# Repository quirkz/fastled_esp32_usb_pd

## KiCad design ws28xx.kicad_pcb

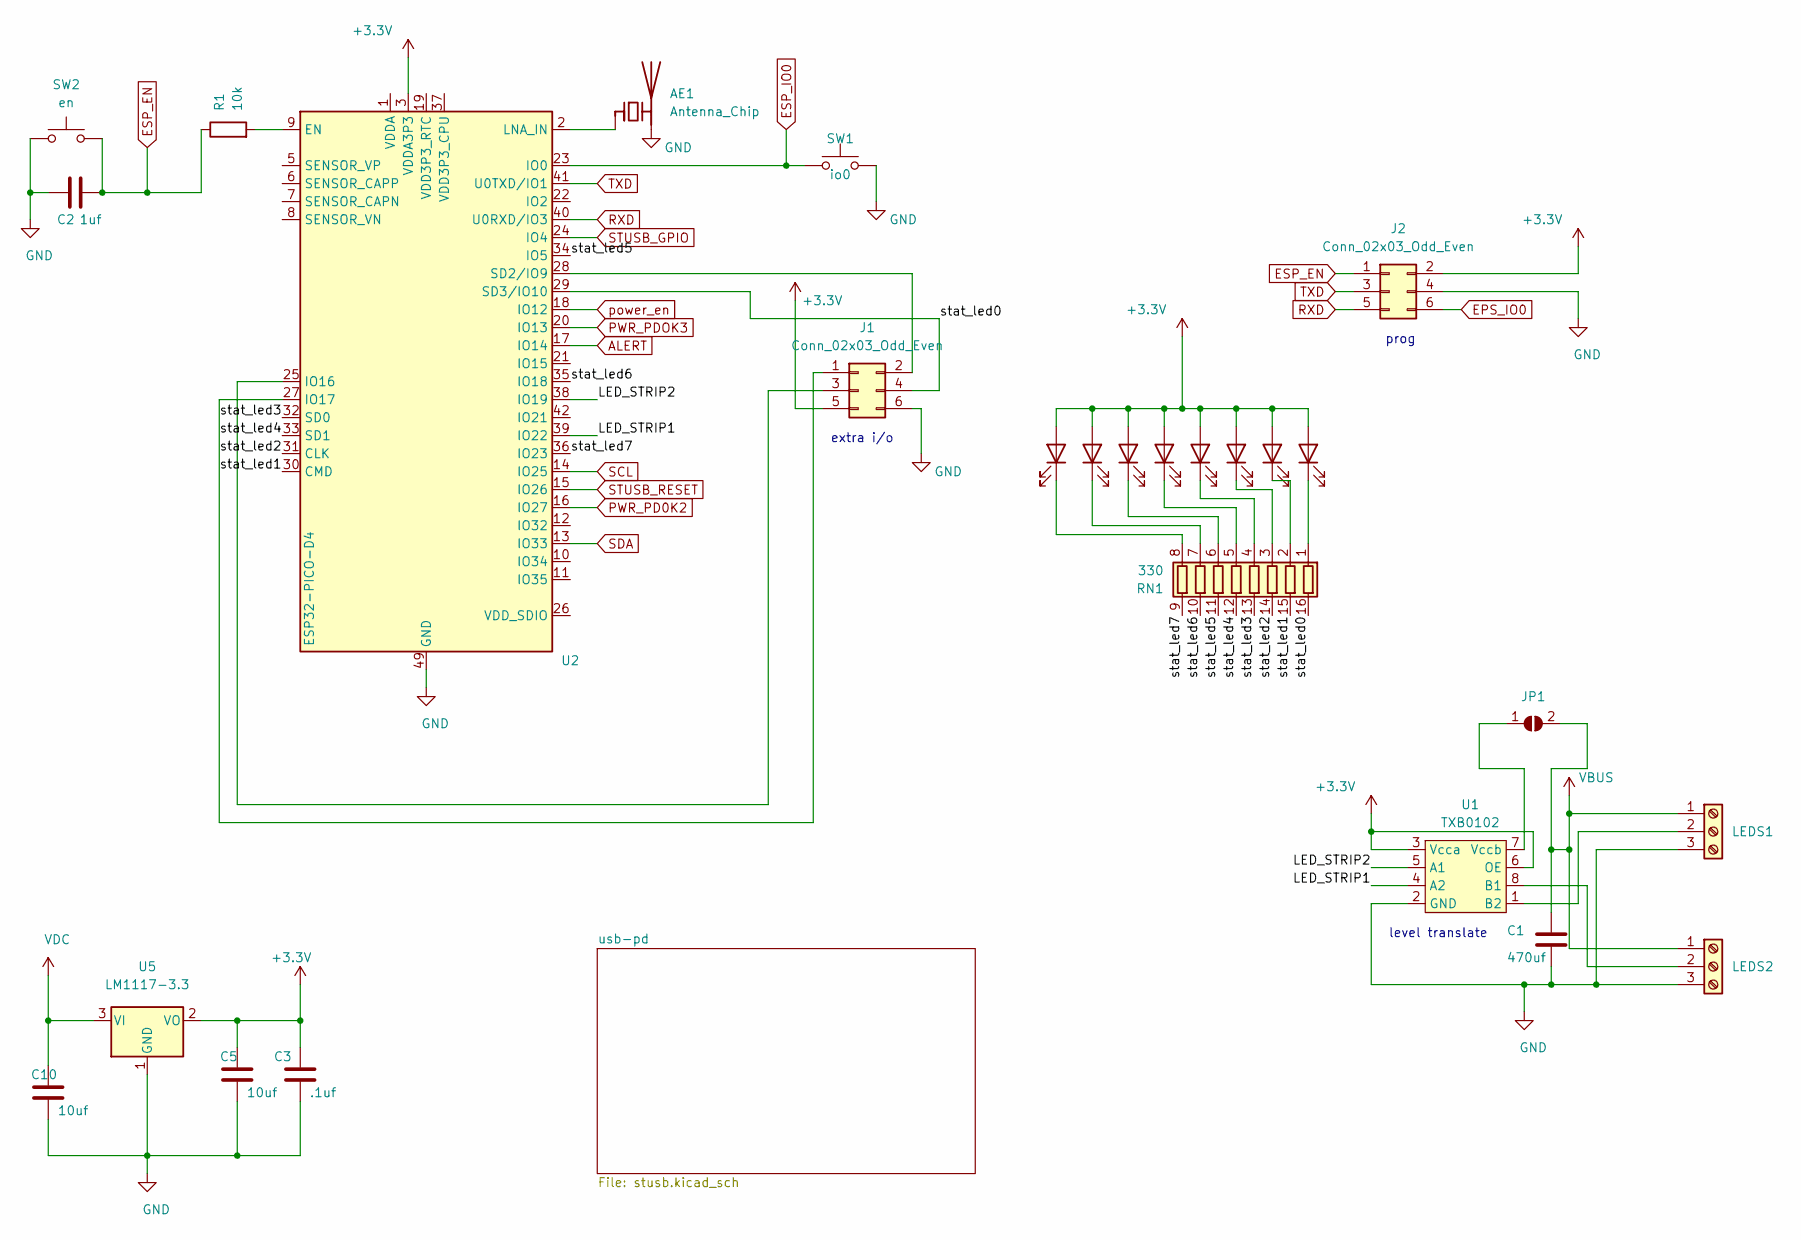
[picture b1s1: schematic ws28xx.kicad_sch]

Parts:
AE1: Antenna_Chip; Texas_SWRA117D_2.4GHz_Right
C1: 470uf; C_Elec_10x10.2
C2: 1uf; C_0603_1608Metric
C3: .1uf; C_0603_1608Metric
C5, C10: 10uf; C_0805_2012Metric
D1, D2, D3, D4, D5, D6, D7, D8: LED; LED_0603_1608Metric
J1, J2: Conn_02x03_Odd_Even; PinHeader_2x03_P1.27mm_Vertical
JP1: SolderJumper_2_Open; PinHeader_1x02_P1.27mm_Vertical
LEDS1: Screw_Terminal_01x0; TerminalBlock_Phoenix_PT-1,5-3-3.5-H_1x03_P3.50mm_Horizontal
LEDS2: Screw_Terminal_01x03; TerminalBlock_Phoenix_PT-1,5-3-3.5-H_1x03_P3.50mm_Horizontal
R1: 10k; R_0603_1608Metric
RN1: 330; R_Array_Convex_8x0602
SW1: io0; SW_Push_1P1T_NO_Vertical
SW2: en; SW_Push_1P1T_NO_Vertical
U1: TXB0102; SOIC-8
U2: ESP32-PICO-D4; QFN-48-1EP_7x7mm_P0.5mm_EP5.3x5.3mm
U5: LM1117-3.3; SOT-223

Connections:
+3V3: C3.1, C5.1, D1.2 (A), D2.2 (A), D3.2 (A), D4.2 (A), D5.2 (A), D6.2 (A), D7.2 (A), D8.2 (A), J1.5, J2.2, U1.3 (Vcca), U1.6 (OE), U2.3 (VDDA3P3), U2.4 (VDDA3P3), U5.2 (VO); also elsewhere on the board
/LED_STRIP1: U1.4 (A2), U2.39 (IO22)
/LED_STRIP2: U1.5 (A1), U2.38 (IO19)
/stat_led0: J1.4, RN1.16 (R1.2), U2.29 (SD3/IO10)
/stat_led1: RN1.15 (R2.2), U2.30 (CMD)
/stat_led2: RN1.14 (R3.2), U2.31 (CLK)
/stat_led3: RN1.13 (R4.2), U2.32 (SD0)
/stat_led4: RN1.12 (R5.2), U2.33 (SD1)
/stat_led5: RN1.11 (R6.2), U2.34 (IO5)
/stat_led6: RN1.10 (R7.2), U2.35 (IO18)
/stat_led7: RN1.9 (R8.2), U2.36 (IO23)
ALERT: U2.17 (IO14); also elsewhere on the board
EPS_IO0: J2.6
ESP_EN: C2.2, J2.1, R1.1, SW2.2; also elsewhere on the board
ESP_IO0: SW1.1, U2.23 (IO0); also elsewhere on the board
GND: AE1.2 (PCB_Trace), C1.2, C2.1, C3.2, C5.2, C10.2, J1.6, J2.4, LEDS1.3, LEDS2.3, SW1.2, SW2.1, U1.2 (GND), U2.49 (GND), U5.1 (GND); also elsewhere on the board
unnamed: AE1.1 (FEED), U2.2 (LNA_IN)
unnamed: D1.1 (K), RN1.8 (R8.1)
unnamed: D2.1 (K), RN1.7 (R7.1)
unnamed: D3.1 (K), RN1.5 (R5.1)
unnamed: D4.1 (K), RN1.6 (R6.1)
unnamed: D5.1 (K), RN1.4 (R4.1)
unnamed: D6.1 (K), RN1.2 (R2.1)
unnamed: D7.1 (K), RN1.1 (R1.1)
unnamed: D8.1 (K), RN1.3 (R3.1)
unnamed: J1.1, U2.27 (IO17)
unnamed: J1.2, U2.28 (SD2/IO9)
unnamed: J1.3, U2.25 (IO16)
unnamed: JP1.1 (A), U1.7 (Vccb)
unnamed: LEDS1.2, U1.1 (B2)
unnamed: LEDS2.2, U1.8 (B1)
unnamed: R1.2, U2.9 (EN)
unnamed: U2.1 (VDDA), U2.43 (VDDA), U2.46 (VDDA)
PWR_PD0K2: U2.16 (IO27); also elsewhere on the board
PWR_PDOK3: U2.20 (IO13); also elsewhere on the board
RXD: J2.5, U2.40 (U0RXD/IO3); also elsewhere on the board
SCL: U2.14 (IO25); also elsewhere on the board
SDA: U2.13 (IO33); also elsewhere on the board
STUSB_GPIO: U2.24 (IO4); also elsewhere on the board
STUSB_RESET: U2.15 (IO26); also elsewhere on the board
TXD: J2.3, U2.41 (U0TXD/IO1); also elsewhere on the board
VBUS: C1.1, JP1.2 (B), LEDS1.1, LEDS2.1; also elsewhere on the board
VDC: C10.1, U5.3 (VI); also elsewhere on the board
power_en: U2.18 (IO12); also elsewhere on the board

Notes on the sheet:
extra i/o
prog
level translate

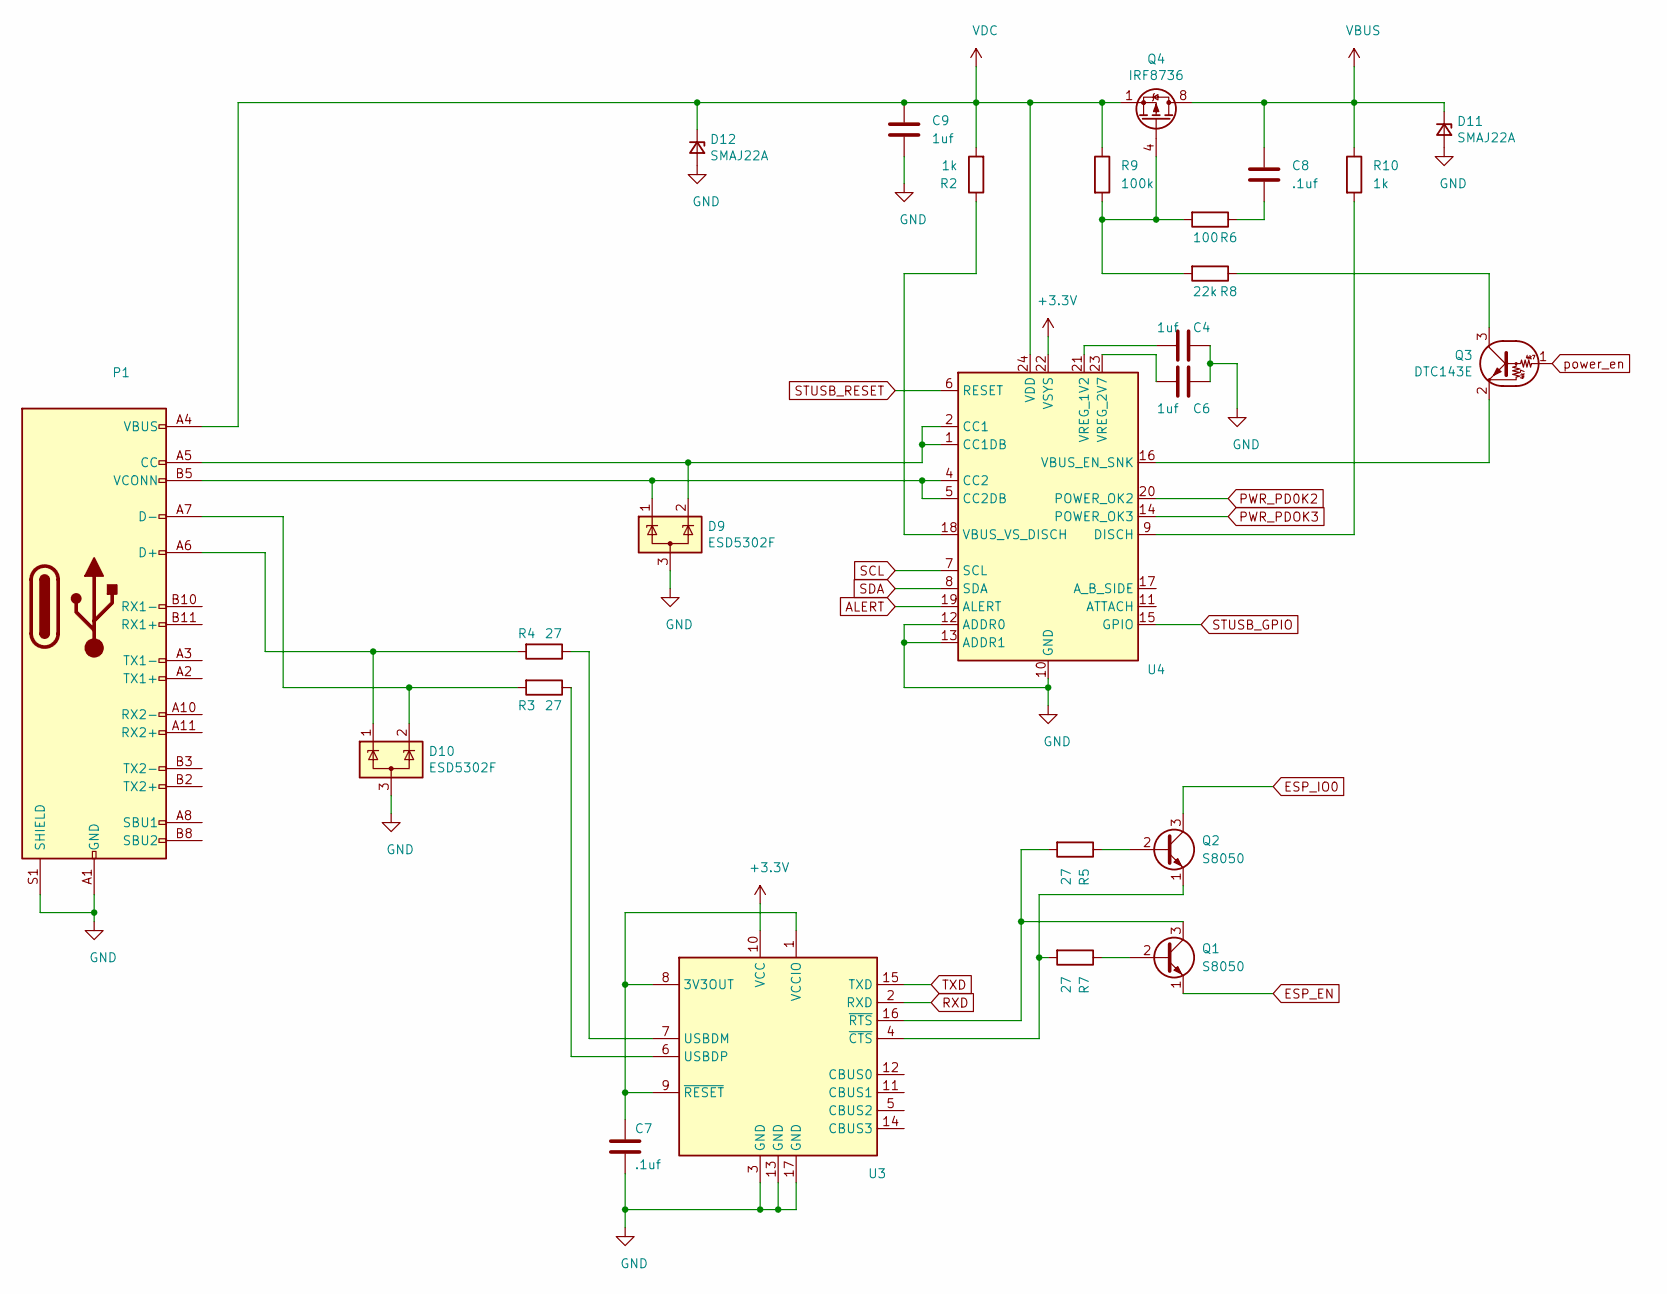
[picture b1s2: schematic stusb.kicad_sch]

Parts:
C4, C6, C9: 1uf; C_0603_1608Metric
C7, C8: .1uf; C_0603_1608Metric
D9, D10: ESD5302F; SOT-23
D11, D12: SMAJ22A; D_SMA
P1: USB_C_Plug; USB_C_Receptacle_Palconn_UTC16-G
Q1, Q2: S8050; SOT-23
Q3: DTC143E; SOT-323_SC-70
Q4: IRF8736; SOIC-8_3.9x4.9mm_P1.27mm
R2, R10: 1k; R_0603_1608Metric
R3, R4, R5, R7: 27; R_0603_1608Metric
R6: 100; R_0603_1608Metric
R8: 22k; R_0603_1608Metric
R9: 100k; R_0603_1608Metric
U3: FT230XQ; QFN-16-1EP_4x4mm_P0.65mm_EP2.1x2.1mm
U4: STUSB4500QTR; QFN-24-1EP_4x4mm_P0.5mm_EP2.7x2.7mm

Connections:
+3V3: U3.10 (VCC), U4.22 (VSYS); also elsewhere on the board
ALERT: U4.19 (ALERT); also elsewhere on the board
ESP_EN: Q1.1 (E); also elsewhere on the board
ESP_IO0: Q2.3 (C); also elsewhere on the board
GND: C4.1, C6.1, C7.2, C9.2, D9.3 (A), D10.3 (A), D11.2 (A), D12.2 (A), P1.A1 (GND), P1.A12 (GND), P1.B1 (GND), P1.B12 (GND), P1.S1 (SHIELD), U3.3 (GND), U3.13 (GND), U3.17 (GND), U4.10 (GND), U4.12 (ADDR0), U4.13 (ADDR1), U4.25 (GND); also elsewhere on the board
unnamed: C4.2, U4.21 (VREG_1V2)
unnamed: C6.2, U4.23 (VREG_2V7)
unnamed: C7.1, U3.1 (VCCIO), U3.8 (3V3OUT), U3.9 (~RESET)
unnamed: C8.2, R6.1
unnamed: D9.1 (K), P1.B5 (VCONN), U4.4 (CC2), U4.5 (CC2DB)
unnamed: D9.2 (K), P1.A5 (CC), U4.1 (CC1DB), U4.2 (CC1)
unnamed: D10.1 (K), P1.A6 (D+), R4.2
unnamed: D10.2 (K), P1.A7 (D-), R3.2
unnamed: Q1.2 (B), R7.1
unnamed: Q1.3 (C), R5.2, U3.16 (~RTS)
unnamed: Q2.1 (E), R7.2, U3.4 (~CTS)
unnamed: Q2.2 (B), R5.1
unnamed: Q3.2 (E), U4.16 (VBUS_EN_SNK)
unnamed: Q3.3 (C), R8.1
unnamed: Q4.4 (G), R6.2, R8.2, R9.2
unnamed: R2.1, U4.18 (VBUS_VS_DISCH)
unnamed: R3.1, U3.6 (USBDP)
unnamed: R4.1, U3.7 (USBDM)
unnamed: R10.2, U4.9 (DISCH)
PWR_PD0K2: U4.20 (POWER_OK2); also elsewhere on the board
PWR_PDOK3: U4.14 (POWER_OK3); also elsewhere on the board
RXD: U3.2 (RXD); also elsewhere on the board
SCL: U4.7 (SCL); also elsewhere on the board
SDA: U4.8 (SDA); also elsewhere on the board
STUSB_GPIO: U4.15 (GPIO); also elsewhere on the board
STUSB_RESET: U4.6 (RESET); also elsewhere on the board
TXD: U3.15 (TXD); also elsewhere on the board
VBUS: C8.1, D11.1 (K), Q4.5 (D), Q4.6 (D), Q4.7 (D), Q4.8 (D), R10.1; also elsewhere on the board
VDC: C9.1, D12.1 (K), P1.A4 (VBUS), P1.A9 (VBUS), P1.B4 (VBUS), P1.B9 (VBUS), Q4.1 (S), Q4.2 (S), Q4.3 (S), R2.2, R9.1, U4.24 (VDD); also elsewhere on the board
power_en: Q3.1 (B); also elsewhere on the board

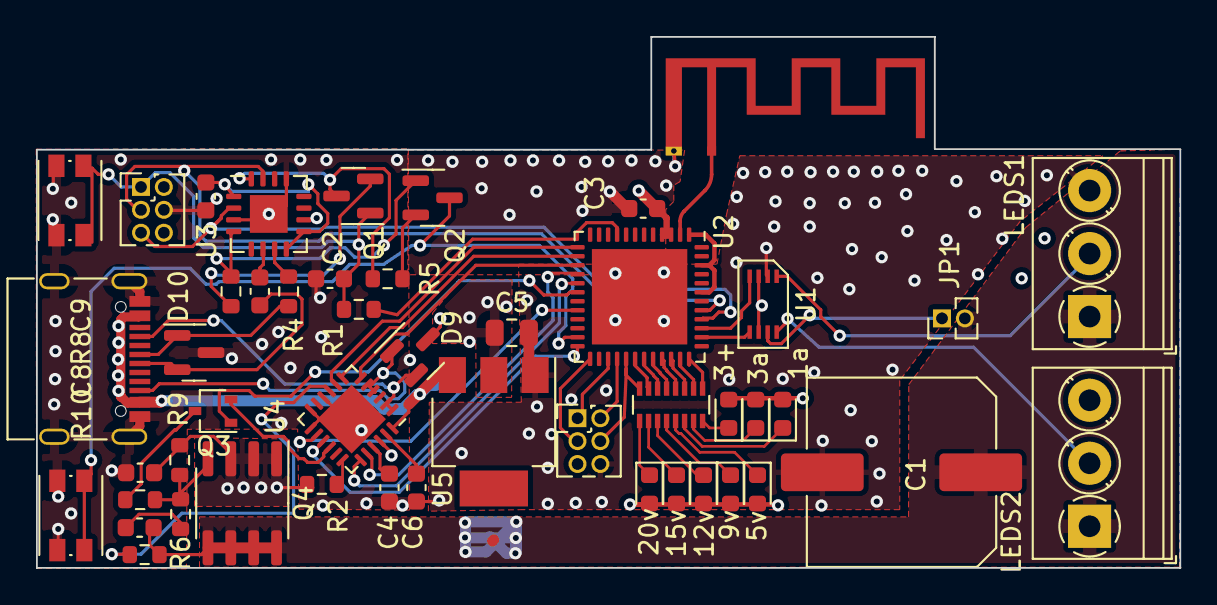
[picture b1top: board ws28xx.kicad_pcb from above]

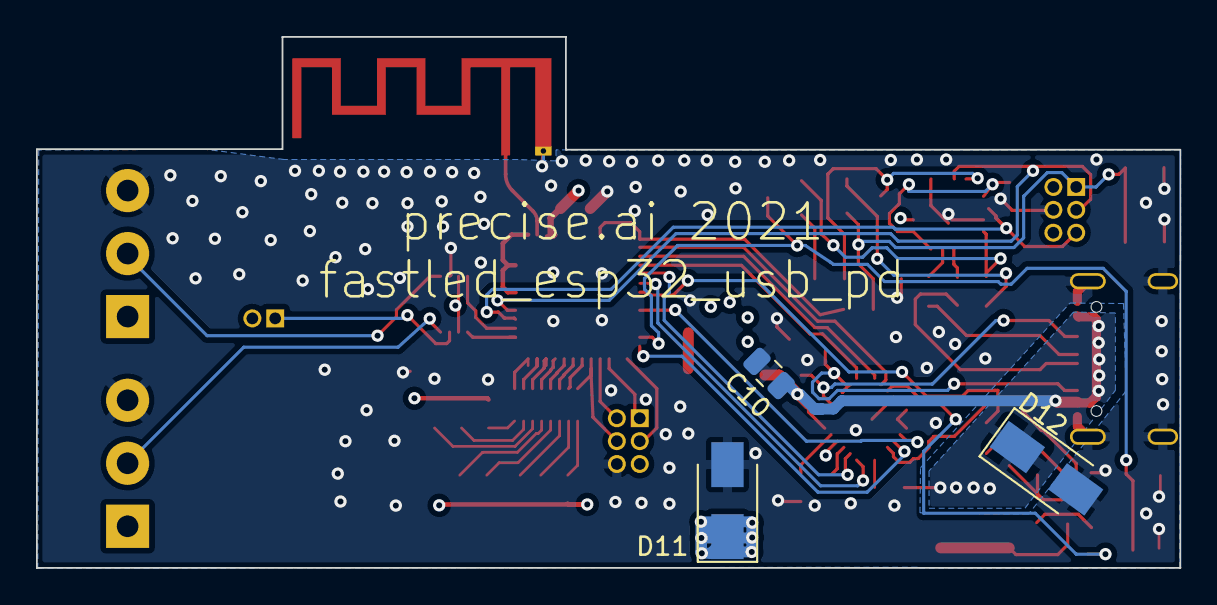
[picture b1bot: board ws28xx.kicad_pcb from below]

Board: 4 copper layers, 63.5 x 29.5 mm, 51 parts (3 on the bottom side), 62 nets.

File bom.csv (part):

"Source:","/home/matt/build/precise/ws28xx/ws28xx.kicad_sch"
"Date:","Wed 17 Mar 2021 02:13:38 PM"
"Tool:","Eeschema 5.99.0-unknown-a82764f43a~117~ubuntu20.10.1"
"Generator:","/usr/share/kicad-nightly/plugins/bom_csv_grouped_by_value.py"
"Component Count:","51"

"Individual Components:"

"Item","Qty","Reference(s)","Value","LibPart","Footprint","Datasheet"
"","","AE1","Antenna_Chip","Device:Antenna_Chip","RF_Antenna:Texas_SWRA117D_2.4GHz_Right","~"
"","","C1","470uf","Device:C","Capacitor_SMD:C_Elec_10x10.2","~"
"","","C2","1uf","Device:C","Capacitor_SMD:C_0603_1608Metric","~"
"","","C3",".1uf","Device:C","Capacitor_SMD:C_0603_1608Metric","~"
"","","C4","1uf","Device:C","Capacitor_SMD:C_0603_1608Metric","~"
"","","C5","10uf","Device:C","Capacitor_SMD:C_0805_2012Metric","~"
"","","C6","1uf","Device:C","Capacitor_SMD:C_0603_1608Metric","~"
"","","C7",".1uf","Device:C","Capacitor_SMD:C_0603_1608Metric","~"
"","","C8",".1uf","Device:C","Capacitor_SMD:C_0603_1608Metric","~"
"","","C9","1uf","Device:C","Capacitor_SMD:C_0603_1608Metric","~"
"","","C10","10uf","Device:C","Capacitor_SMD:C_0805_2012Metric","~"
"","","D1","LED","Device:LED","LED_SMD:LED_0603_1608Metric","~"
"","","D2","LED","Device:LED","LED_SMD:LED_0603_1608Metric","~"
"","","D3","LED","Device:LED","LED_SMD:LED_0603_1608Metric","~"
"","","D4","LED","Device:LED","LED_SMD:LED_0603_1608Metric","~"
"","","D5","LED","Device:LED","LED_SMD:LED_0603_1608Metric","~"
"","","D6","LED","Device:LED","LED_SMD:LED_0603_1608Metric","~"
"","","D7","LED","Device:LED","LED_SMD:LED_0603_1608Metric","~"
"","","D8","LED","Device:LED","LED_SMD:LED_0603_1608Metric","~"
"","","D9","ESD5302F","Power_Protection:SP0502BAHT","Package_TO_SOT_SMD:SOT-23","http://www.littelfuse.com/~/media/files/littelfuse/technical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"
"","","D10","ESD5302F","Power_Protection:SP0502BAHT","Package_TO_SOT_SMD:SOT-23","http://www.littelfuse.com/~/media/files/littelfuse/technical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"
"","","D11","SMAJ22A ","Device:D_Zener_Small","Diode_SMD:D_SMA","~"
"","","D12","SMAJ22A ","Device:D_Zener_Small","Diode_SMD:D_SMA","~"
"","","J1","Conn_02x03_Odd_Even","Connector_Generic:Conn_02x03_Odd_Even","Connector_PinHeader_1.27mm:PinHeader_2x03_P1.27mm_Vertical","~"
"","","J2","Conn_02x03_Odd_Even","Connector_Generic:Conn_02x03_Odd_Even","Connector_PinHeader_1.27mm:PinHeader_2x03_P1.27mm_Vertical","~"
"","","JP1","SolderJumper_2_Open","Jumper:SolderJumper_2_Open","Connector_PinHeader_1.27mm:PinHeader_1x02_P1.27mm_Vertical","~"
"","","LEDS1","Screw_Terminal_01x0","Connector:Screw_Terminal_01x03","TerminalBlock_Phoenix:TerminalBlock_Phoenix_PT-1,5-3-3.5-H_1x03_P3.50mm_Horizontal","~"
"","","LEDS2","Screw_Terminal_01x03","Connector:Screw_Terminal_01x03","TerminalBlock_Phoenix:TerminalBlock_Phoenix_PT-1,5-3-3.5-H_1x03_P3.50mm_Horizontal","~"
"","","P1","USB_C_Plug","Connector:USB_C_Plug","Connector_USB:USB_C_Receptacle_Palconn_UTC16-G","https://www.usb.org/sites/default/files/documents/usb_type-c.zip"
"","","Q1","S8050","Transistor_BJT:S8050","Package_TO_SOT_SMD:SOT-23","http://www.unisonic.com.tw/datasheet/S8050.pdf"
"","","Q2","S8050","Transistor_BJT:S8050","Package_TO_SOT_SMD:SOT-23","http://www.unisonic.com.tw/datasheet/S8050.pdf"
"","","Q3","DTC143E","-Discrete:DTC143E","Package_TO_SOT_SMD:SOT-323_SC-70",""
"","","Q4","IRF8736","Transistor_FET:FDS9435A","precise:SOIC-8_3.9x4.9mm_P1.27mm","https://www.onsemi.com/pub/Collateral/FDS9435A-D.PDF"
"","","R1","10k","Device:R","Resistor_SMD:R_0603_1608Metric","~"
"","","R2","1k","Device:R","Resistor_SMD:R_0603_1608Metric","~"
"","","R3","27","Device:R","Resistor_SMD:R_0603_1608Metric","~"
"","","R4","27","Device:R","Resistor_SMD:R_0603_1608Metric","~"
"","","R5","27","Device:R","Resistor_SMD:R_0603_1608Metric","~"
"","","R6","100","Device:R","Resistor_SMD:R_0603_1608Metric","~"
"","","R7","27","Device:R","Resistor_SMD:R_0603_1608Metric","~"
"","","R8","22k","Device:R","Resistor_SMD:R_0603_1608Metric","~"
"","","R9","100k","Device:R","Resistor_SMD:R_0603_1608Metric","~"
"","","R10","1k","Device:R","Resistor_SMD:R_0603_1608Metric","~"
"","","RN1","330","Device:R_Pack08","Resistor_SMD:R_Array_Convex_8x0602","~"
"","","SW1","io0","Switch:SW_Push","precise:SW_Push_1P1T_NO_Vertical","~"
"","","SW2","en","Switch:SW_Push","precise:SW_Push_1P1T_NO_Vertical","~"
"","","U1","TXB0102","precise:TXB0102","precise:SOIC-8",""
"","","U2","ESP32-PICO-D4","RF_Module:ESP32-PICO-D4","Package_DFN_QFN:QFN-48-1EP_7x7mm_P0.5mm_EP5.3x5.3mm","https://www.espressif.com/sites/default/files/documentation/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"
"","","U3","FT230XQ","Interface_USB:FT230XQ","Package_DFN_QFN:QFN-16-1EP_4x4mm_P0.65mm_EP2.1x2.1mm","https://www.ftdichip.com/Support/Documents/DataSheets/ICs/DS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"
"","","U4","STUSB4500QTR","Interface_USB:STUSB4500QTR","Package_DFN_QFN:QFN-24-1EP_4x4mm_P0.5mm_EP2.7x2.7mm","https://www.st.com/resource/en/datasheet/stusb4500.pdf"
"","","U5","LM1117-3.3","Regulator_Linear:LM1117-3.3","Package_TO_SOT_SMD:SOT-223","http://www.ti.com/lit/ds/symlink/lm1117.pdf"



"Collated Components:"

"Item","Qty","Reference(s)","Value","LibPart","Footprint","Datasheet"
"1","1","AE1","Antenna_Chip","Device:Antenna_Chip","RF_Antenna:Texas_SWRA117D_2.4GHz_Right","~"
"2","1","C1","470uf","Device:C","Capacitor_SMD:C_Elec_10x10.2","~"
"3","4","C2, C4, C6, C9","1uf","Device:C","Capacitor_SMD:C_0603_1608Metric","~"
"4","3","C3, C7, C8",".1uf","Device:C","Capacitor_SMD:C_0603_1608Metric","~"
"5","2","C5, C10","10uf","Device:C","Capacitor_SMD:C_0805_2012Metric","~"
"6","8","D1, D2, D3, D4, D5, D6, D7, D8","LED","Device:LED","LED_SMD:LED_0603_1608Metric","~"
"7","2","D9, D10","ESD5302F","Power_Protection:SP0502BAHT","Package_TO_SOT_SMD:SOT-23","http://www.littelfuse.com/~/media/files/littelfuse/technical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"
"8","2","D11, D12","SMAJ22A ","Device:D_Zener_Small","Diode_SMD:D_SMA","~"
"9","2","J1, J2","Conn_02x03_Odd_Even","Connector_Generic:Conn_02x03_Odd_Even","Connector_PinHeader_1.27mm:PinHeader_2x03_P1.27mm_Vertical","~"
"10","1","JP1","SolderJumper_2_Open","Jumper:SolderJumper_2_Open","Connector_PinHeader_1.27mm:PinHeader_1x02_P1.27mm_Vertical","~"
"11","1","LEDS1","Screw_Terminal_01x0","Connector:Screw_Terminal_01x03","TerminalBlock_Phoenix:TerminalBlock_Phoenix_PT-1,5-3-3.5-H_1x03_P3.50mm_Horizontal","~"
"12","1","LEDS2","Screw_Terminal_01x03","Connector:Screw_Terminal_01x03","TerminalBlock_Phoenix:TerminalBlock_Phoenix_PT-1,5-3-3.5-H_1x03_P3.50mm_Horizontal","~"
"13","1","P1","USB_C_Plug","Connector:USB_C_Plug","Connector_USB:USB_C_Receptacle_Palconn_UTC16-G","https://www.usb.org/sites/default/files/documents/usb_type-c.zip"
"14","2","Q1, Q2","S8050","Transistor_BJT:S8050","Package_TO_SOT_SMD:SOT-23","http://www.unisonic.com.tw/datasheet/S8050.pdf"
"15","1","Q3","DTC143E","-Discrete:DTC143E","Package_TO_SOT_SMD:SOT-323_SC-70",""
"16","1","Q4","IRF8736","Transistor_FET:FDS9435A","precise:SOIC-8_3.9x4.9mm_P1.27mm","https://www.onsemi.com/pub/Collateral/FDS9435A-D.PDF"
"17","1","R1","10k","Device:R","Resistor_SMD:R_0603_1608Metric","~"
"18","2","R2, R10","1k","Device:R","Resistor_SMD:R_0603_1608Metric","~"
"19","4","R3, R4, R5, R7","27","Device:R","Resistor_SMD:R_0603_1608Metric","~"
"20","1","R6","100","Device:R","Resistor_SMD:R_0603_1608Metric","~"
"21","1","R8","22k","Device:R","Resistor_SMD:R_0603_1608Metric","~"
"22","1","R9","100k","Device:R","Resistor_SMD:R_0603_1608Metric","~"
"23","1","RN1","330","Device:R_Pack08","Resistor_SMD:R_Array_Convex_8x0602","~"
"24","1","SW1","io0","Switch:SW_Push","precise:SW_Push_1P1T_NO_Vertical","~"
"25","1","SW2","en","Switch:SW_Push","precise:SW_Push_1P1T_NO_Vertical","~"
"26","1","U1","TXB0102","precise:TXB0102","precise:SOIC-8",""
"27","1","U2","ESP32-PICO-D4","RF_Module:ESP32-PICO-D4","Package_DFN_QFN:QFN-48-1EP_7x7mm_P0.5mm_EP5.3x5.3mm","https://www.espressif.com/sites/default/files/documentation/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"
"28","1","U3","FT230XQ","Interface_USB:FT230XQ","Package_DFN_QFN:QFN-16-1EP_4x4mm_P0.65mm_EP2.1x2.1mm","https://www.ftdichip.com/Support/Documents/DataSheets/ICs/DS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"
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
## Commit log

2021-03-07 first
2021-03-07 routed
2021-03-08 routing
2021-03-17 tweaks
2021-03-21 sent to seeed
2021-03-21 update render
